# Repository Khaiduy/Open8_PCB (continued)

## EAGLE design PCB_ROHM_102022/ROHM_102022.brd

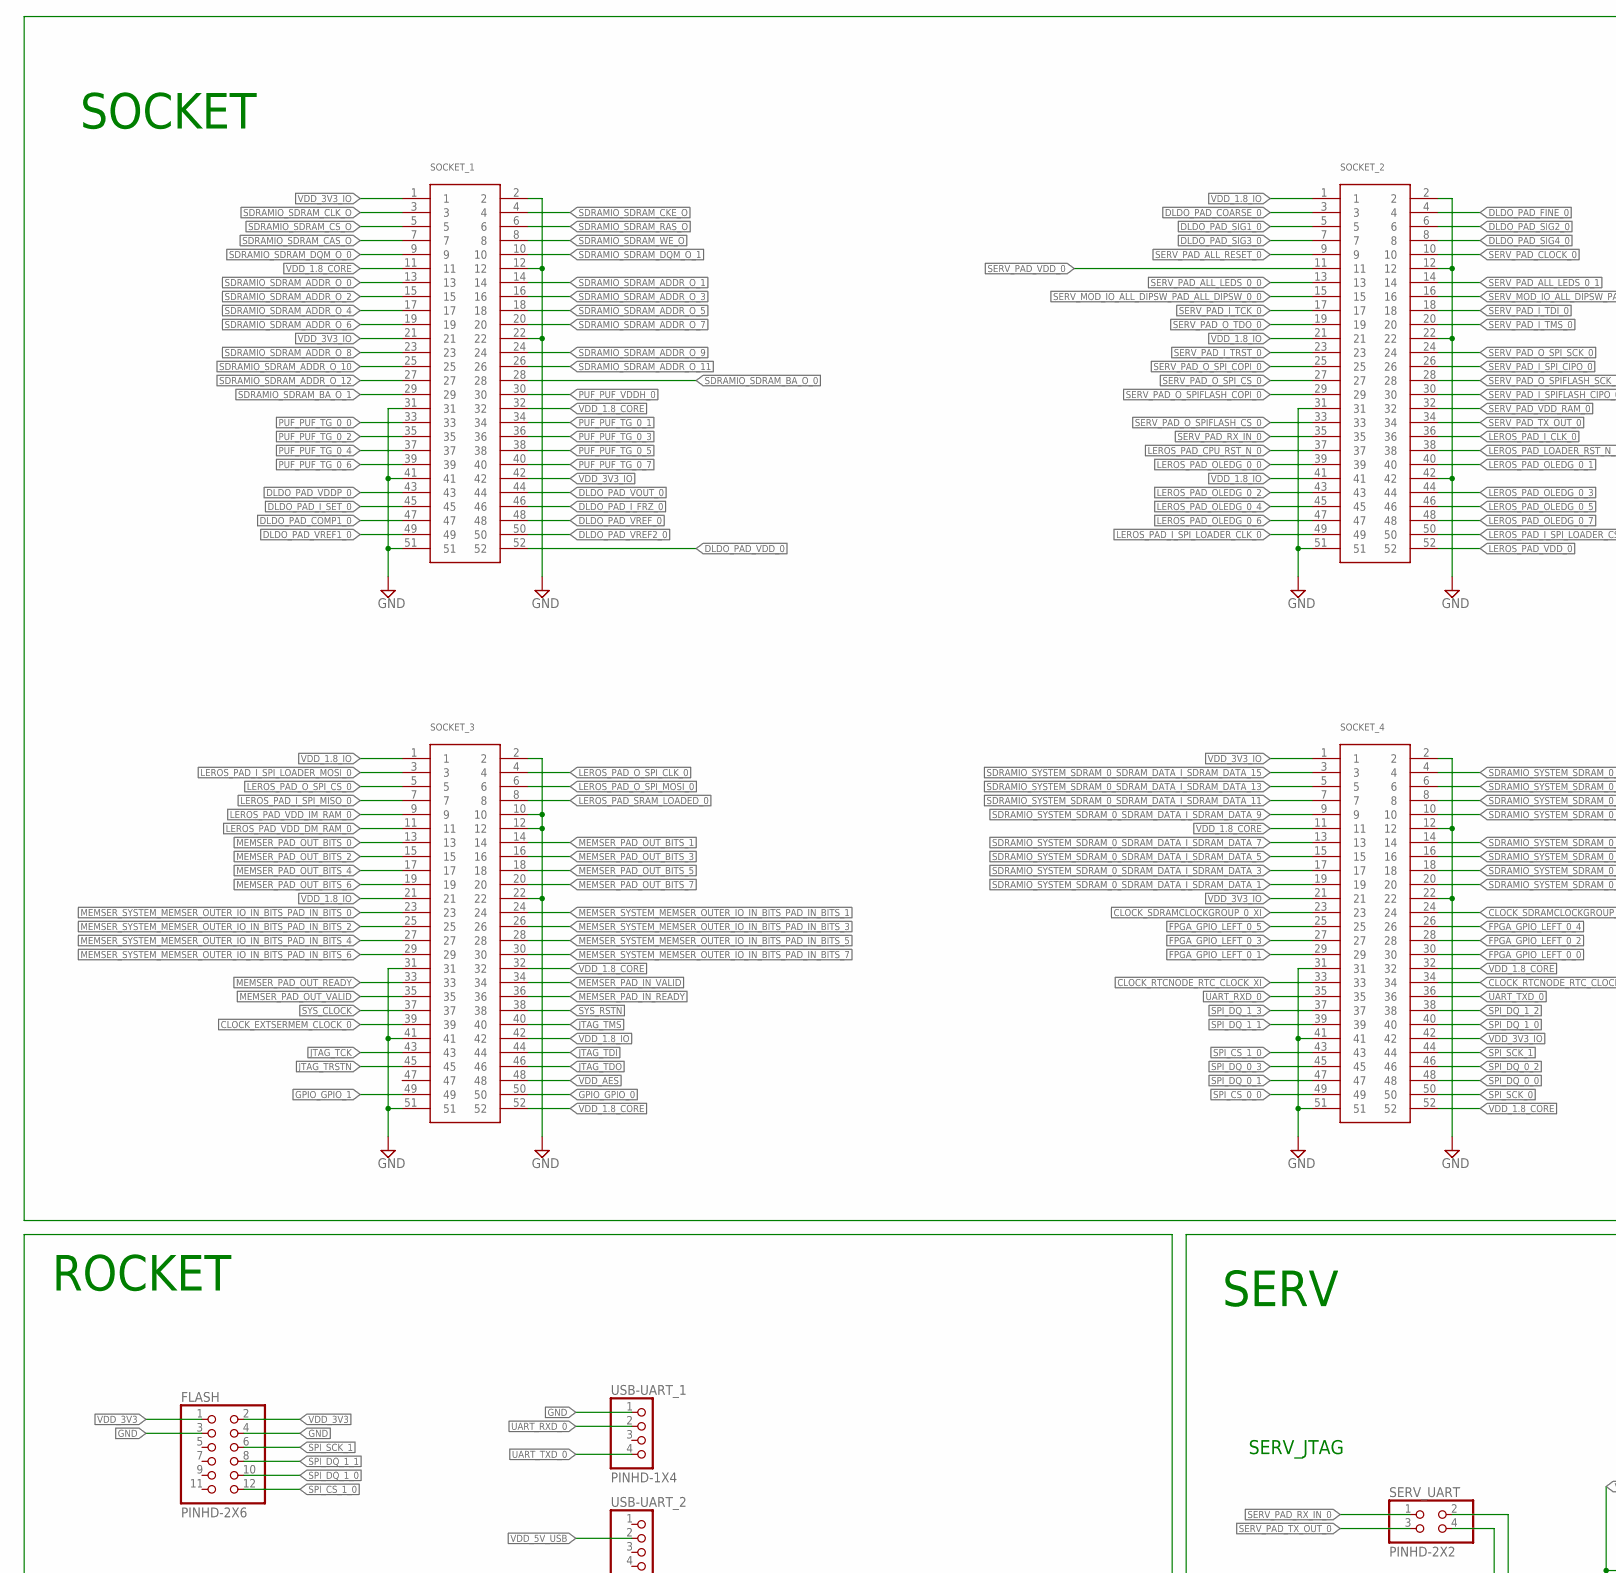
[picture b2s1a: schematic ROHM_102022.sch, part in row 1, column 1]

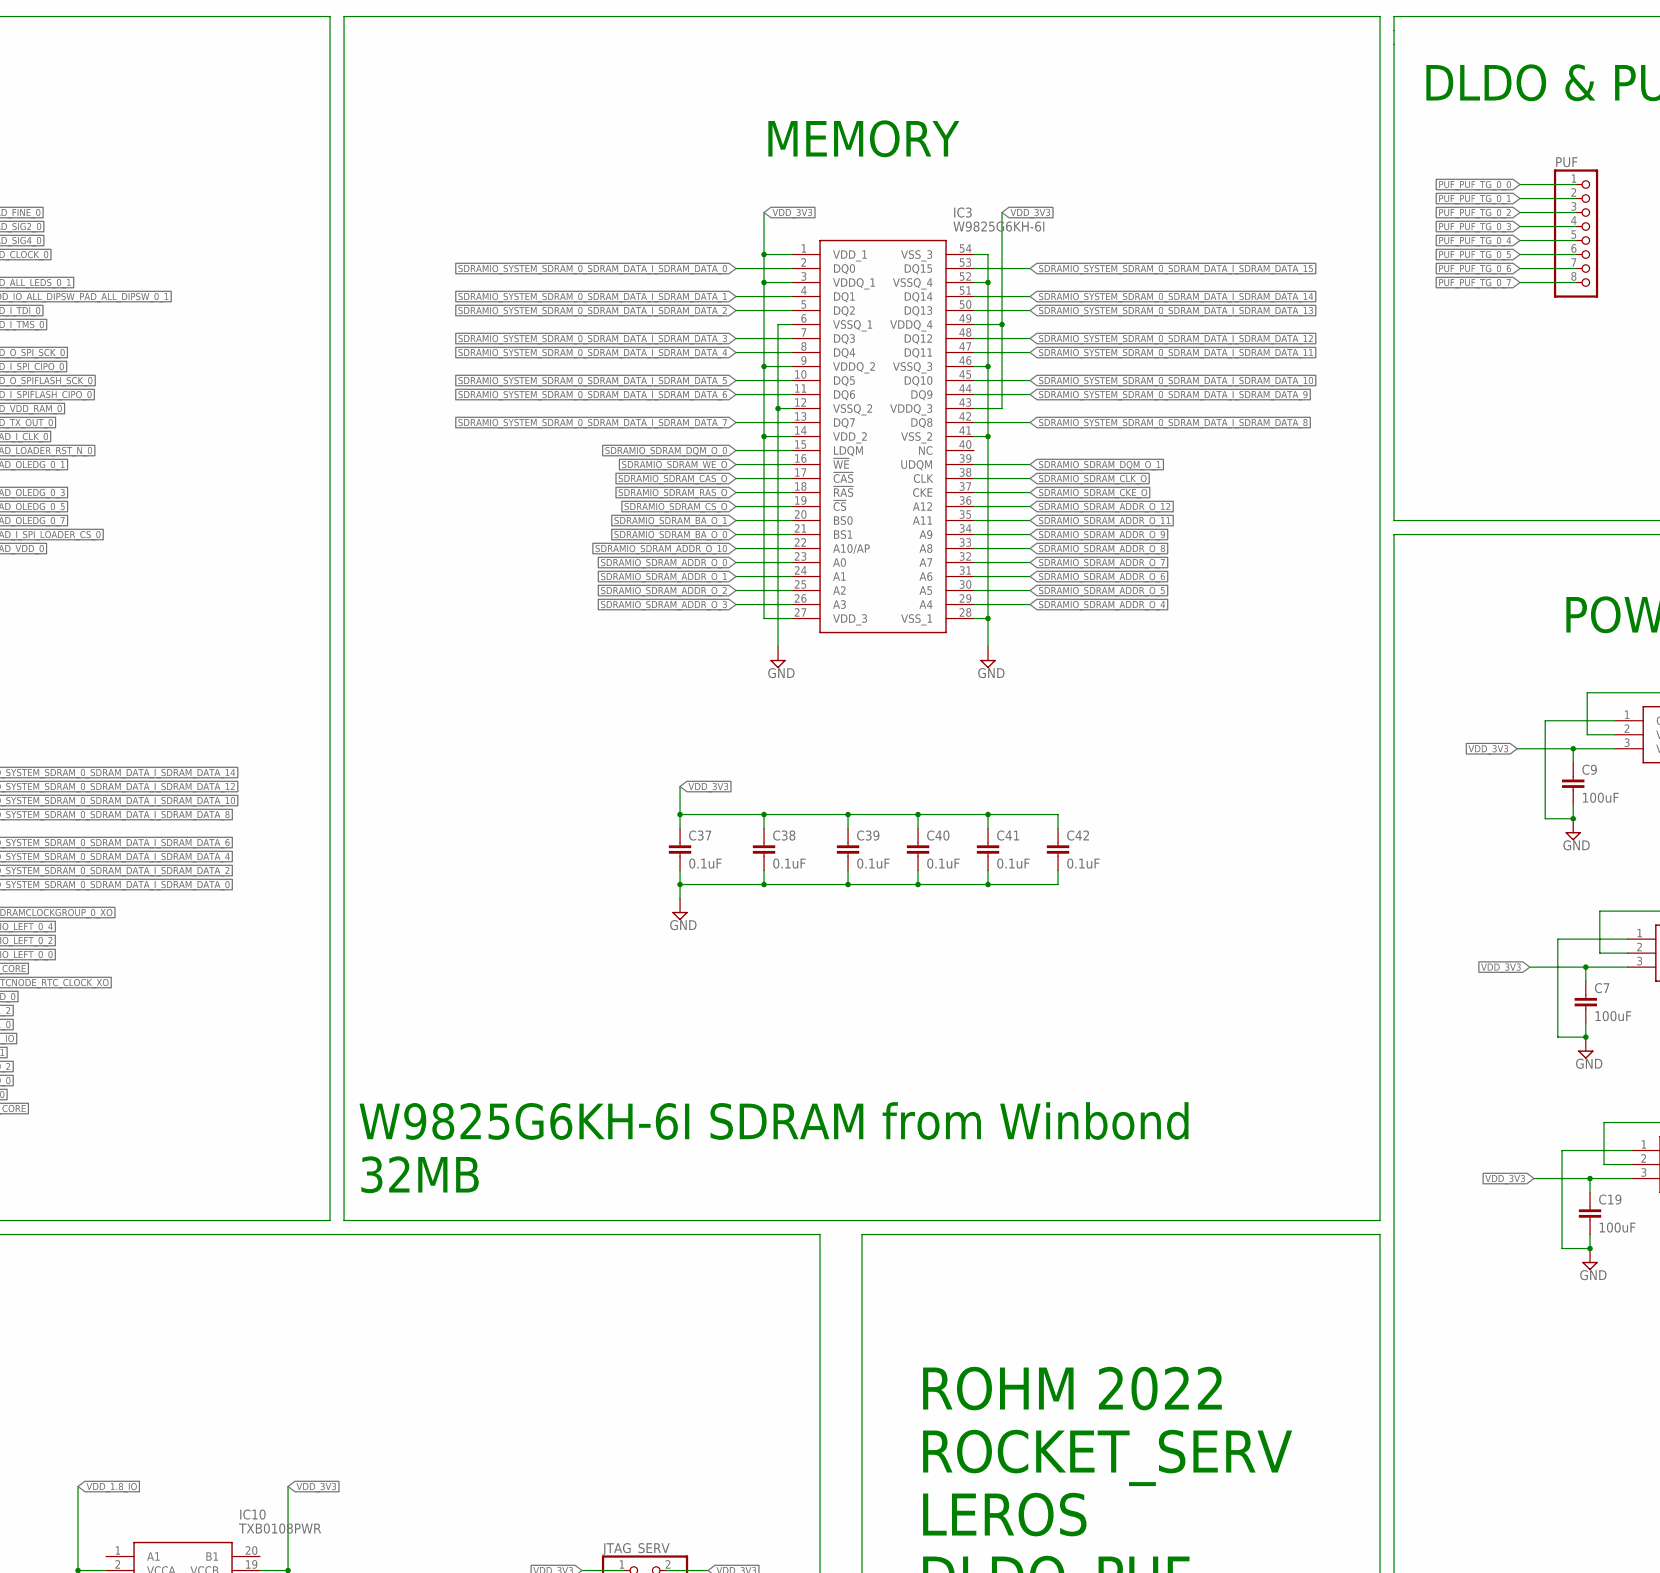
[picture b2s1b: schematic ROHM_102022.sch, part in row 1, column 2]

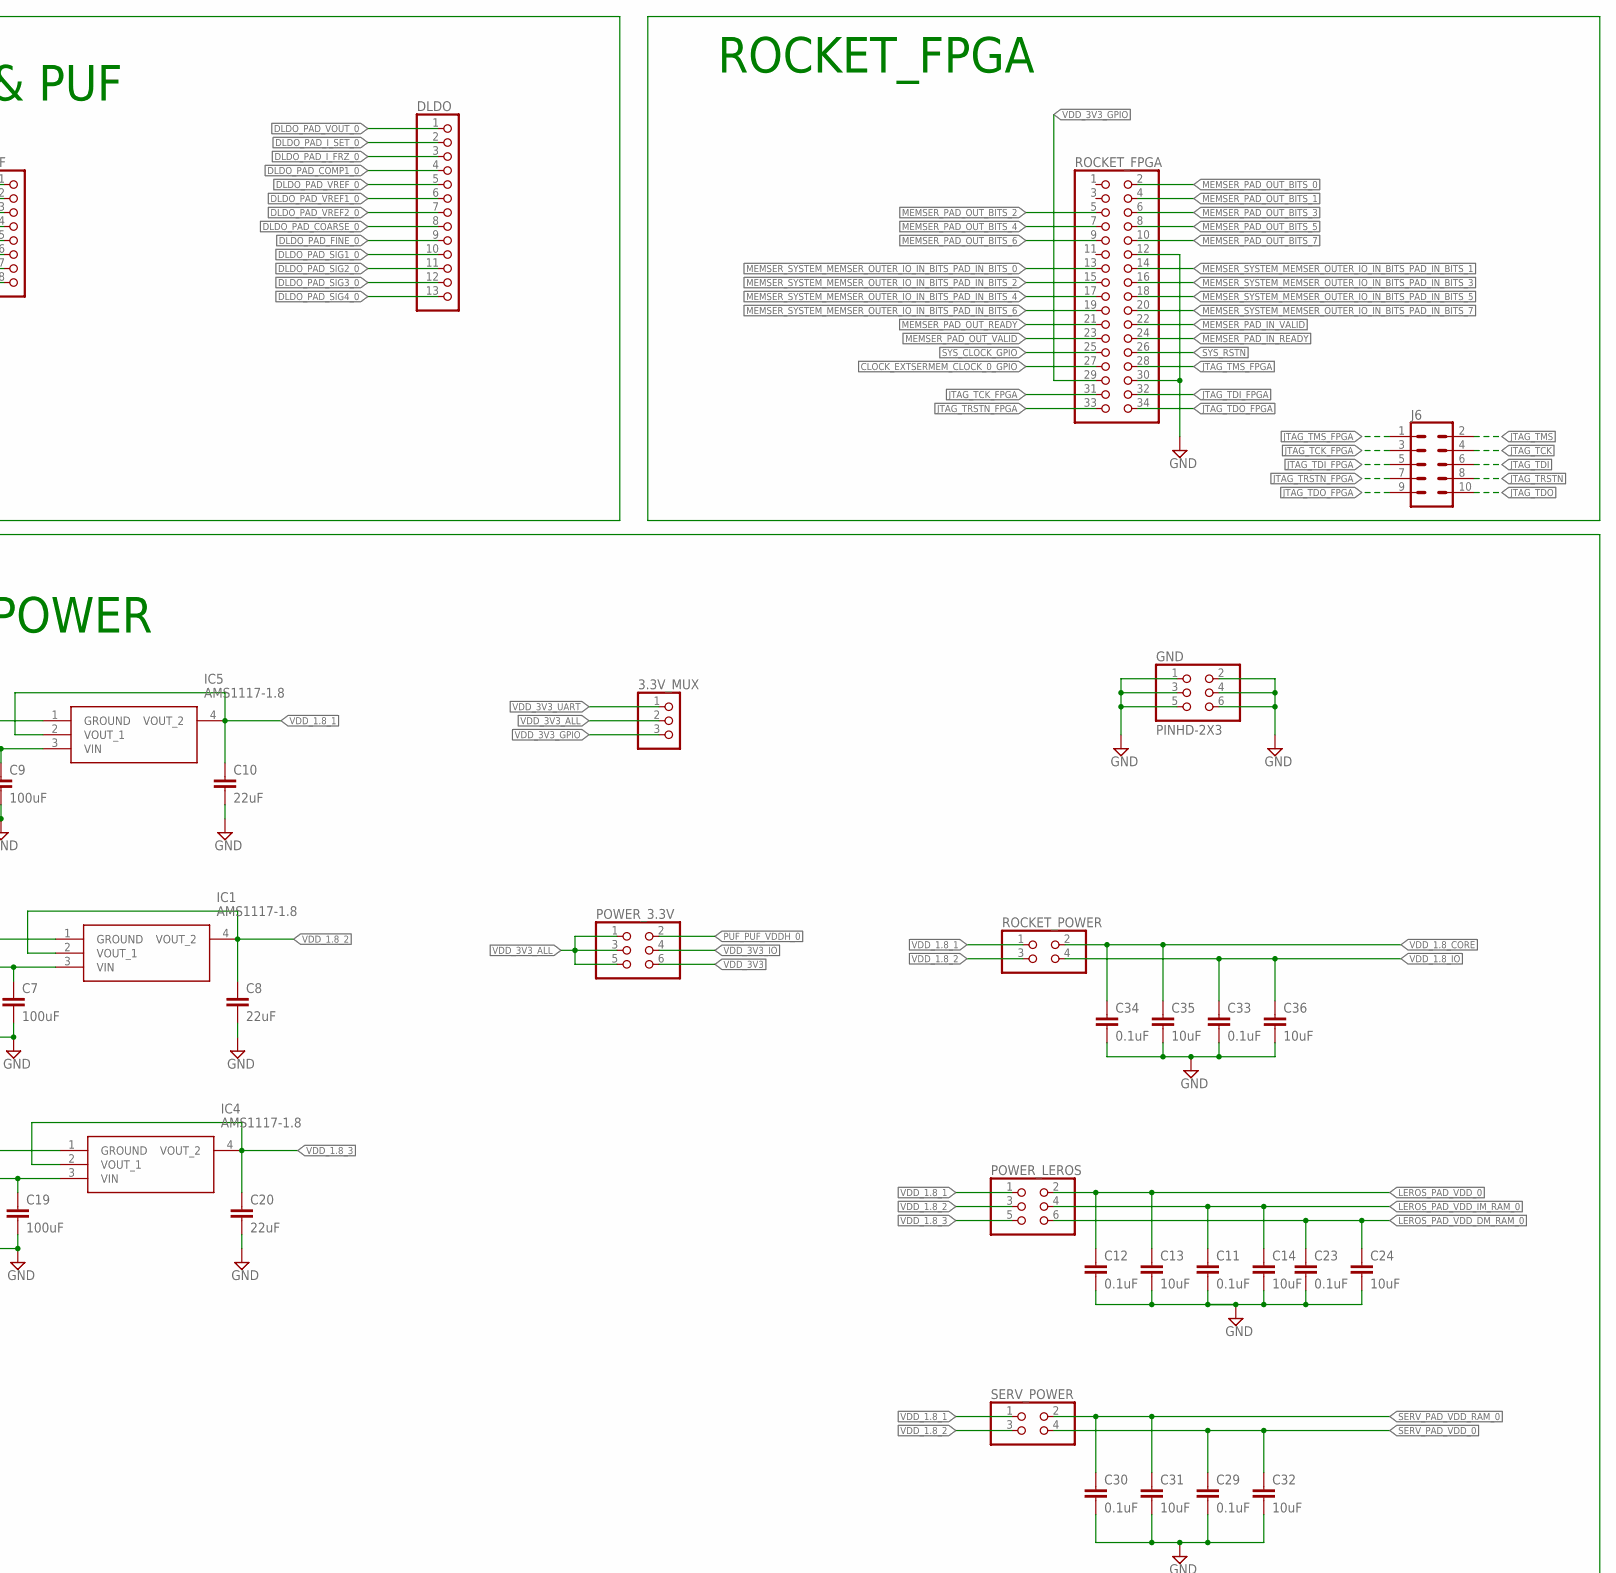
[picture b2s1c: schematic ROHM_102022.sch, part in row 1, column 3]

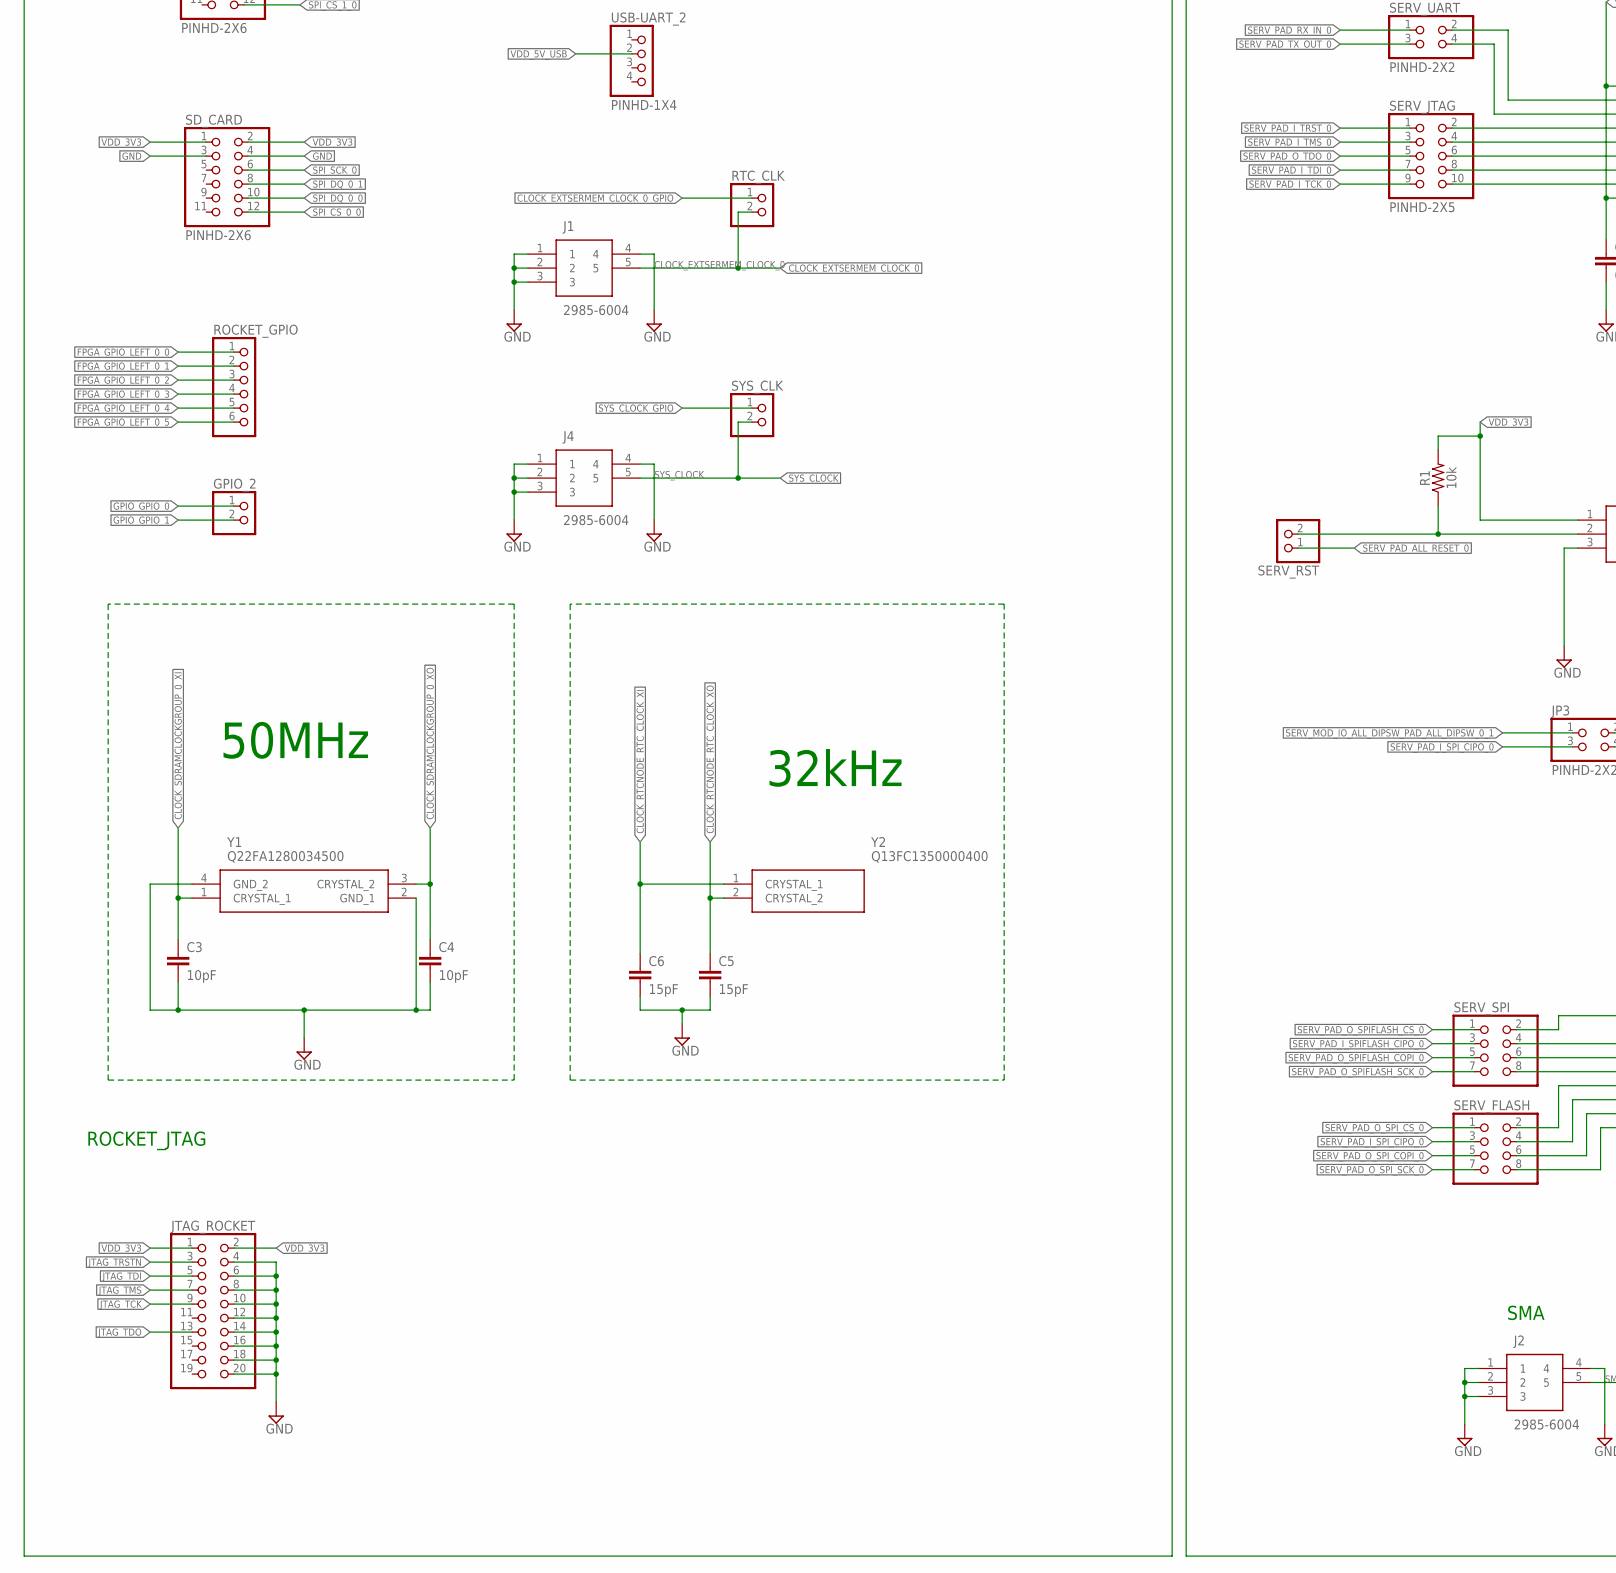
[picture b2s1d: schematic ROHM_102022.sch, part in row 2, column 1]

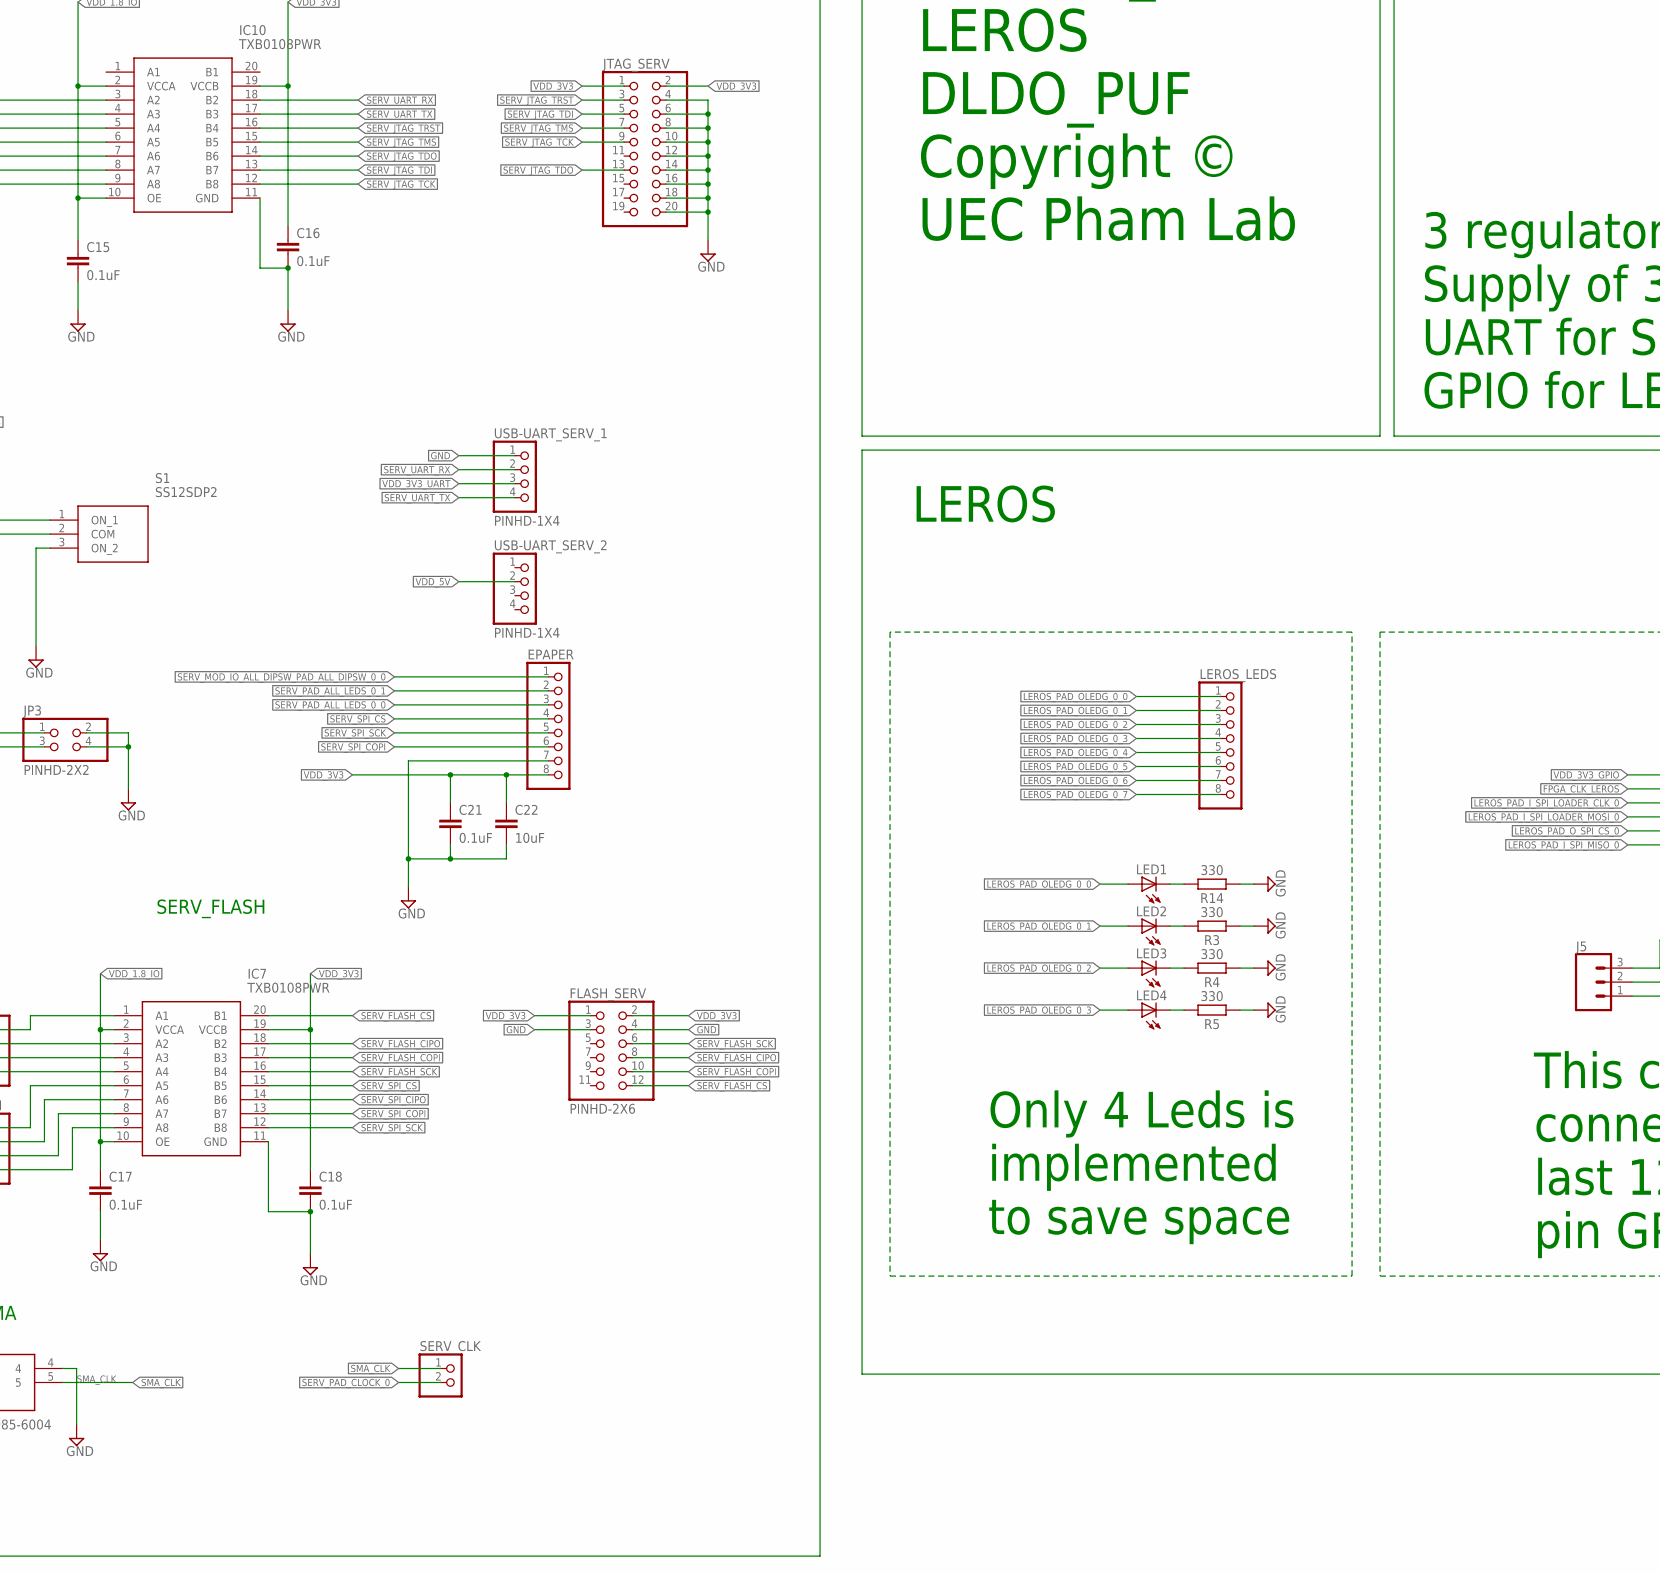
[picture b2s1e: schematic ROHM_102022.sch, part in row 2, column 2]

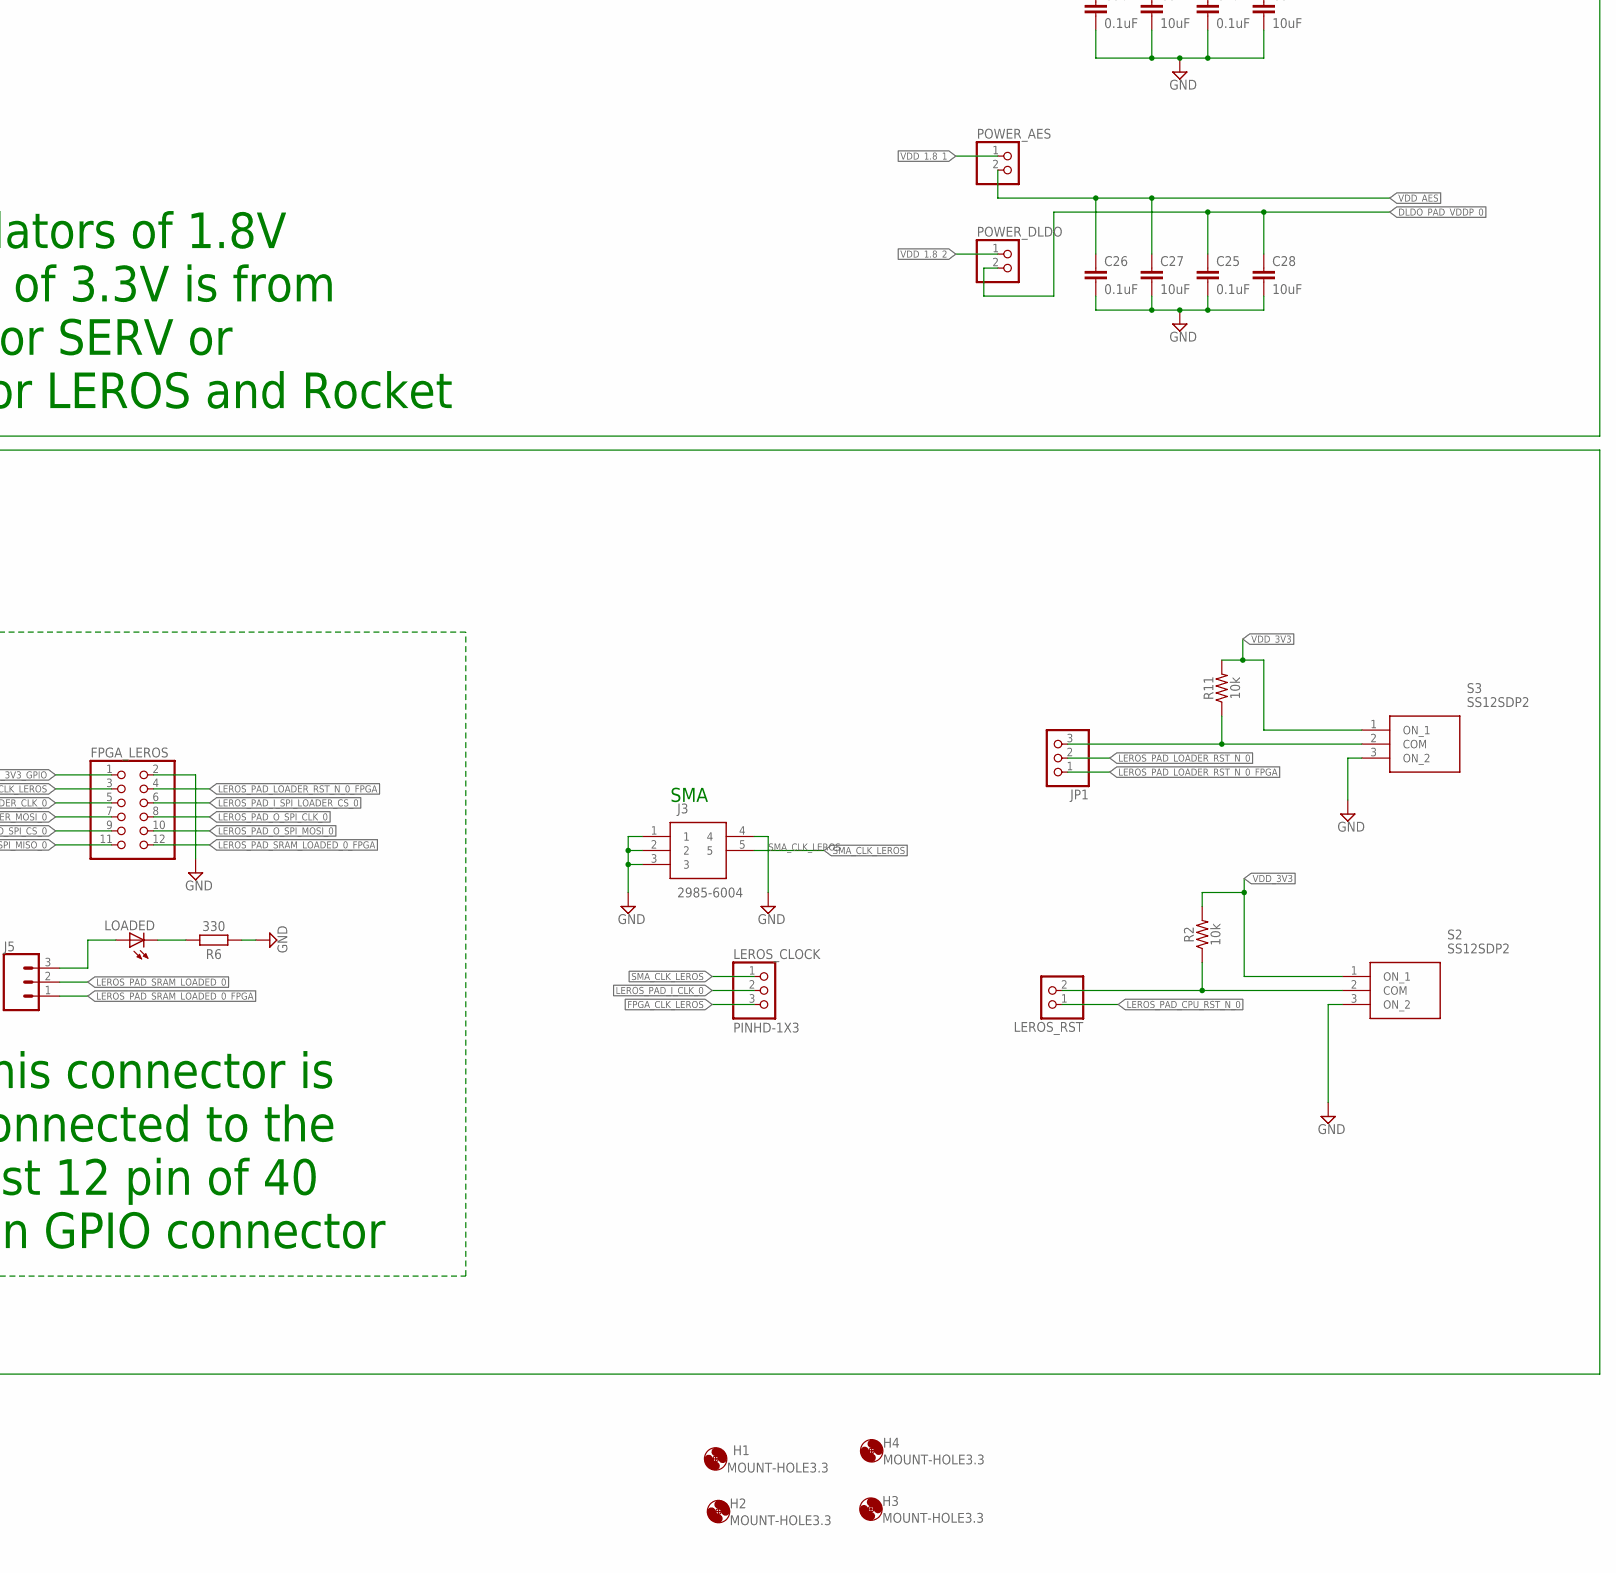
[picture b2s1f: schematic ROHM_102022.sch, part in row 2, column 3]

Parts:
3.3V_MUX: PINHD-1X3; 1X03
C3, C4: 10pF; 1206
C5, C6: 15pF; 1206
C7, C9, C19: 100uF; 1206
C8, C10, C20: 22uF; 1206
C11, C12, C15, C16, C17, C18, C21, C23, C25, C26, C29, C30, C33, C34, C37, C38, C39, C40, C41, C42: 0.1uF; 1206
C13, C14, C22, C24, C27, C28, C31, C32, C35, C36: 10uF; 1206
DLDO: PINHD-1X13; 1X13
EPAPER: PINHD-1X8; 1X08
FLASH: PINHD-2X6; 2X06
FLASH_SERV: PINHD-2X6; 2X06
FPGA_LEROS: PINHD-2X6; 2X06
GND: PINHD-2X3; 2X03
GPIO_2: PINHD-1X2; 1X02
H1, H2, H3, H4: MOUNT-HOLE3.3; 3,3
IC1, IC4, IC5: AMS1117-1.8; SOT229P700X180-4N
IC3: W9825G6KH-6I; SOP80P1176X120-54N
IC7, IC10: TXB0108PWR; SOP65P640X120-20N
J1, J2, J3, J4: 2985-6004; 29856004
J5: CONN_03; 1X03
J6: CONN_05X2PTH; 2X5
JP1: PINHD-1X3; 1X03
JP3: PINHD-2X2; 2X02
JTAG_ROCKET: PINHD-2X10; 2X10
JTAG_SERV: PINHD-2X10; 2X10
LED1, LED2, LED3, LED4: LEDCHIPLED_0805; CHIPLED_0805
LEROS_CLOCK: PINHD-1X3; 1X03
LEROS_LEDS: PINHD-1X8; 1X08
LEROS_RST: PINHD-1X2; 1X02
LOADED: LEDCHIPLED_0805; CHIPLED_0805
POWER_3.3V: PINHD-2X3; 2X03
POWER_AES: PINHD-1X2; 1X02
POWER_DLDO: PINHD-1X2; 1X02
POWER_LEROS: PINHD-2X3; 2X03
PUF: PINHD-1X8; 1X08
R1, R2, R11: 10k; 1206
R3, R4, R5, R6, R14: 330; RESC3216X70
ROCKET_FPGA: PINHD-2X17; 2X17
ROCKET_GPIO: PINHD-1X6; 1X06
ROCKET_POWER: PINHD-2X2; 2X02
RTC_CLK: PINHD-1X2; 1X02
S1, S2, S3: SS12SDP2
SD_CARD: PINHD-2X6; 2X06
SERV_CLK: PINHD-1X2; 1X02
SERV_FLASH: PINHD-2X4; 2X04
SERV_JTAG: PINHD-2X5; 2X05
SERV_POWER: PINHD-2X2; 2X02
SERV_RST: PINHD-1X2; 1X02
SERV_SPI: PINHD-2X4; 2X04
SERV_UART: PINHD-2X2; 2X02
SOCKET_1, SOCKET_2, SOCKET_3, SOCKET_4: 2X26_HEADER
SYS_CLK: PINHD-1X2; 1X02
USB-UART_1, USB-UART_2: PINHD-1X4; 1X04
USB-UART_SERV_1, USB-UART_SERV_2: PINHD-1X4; 1X04
Y1: Q22FA1280034500
Y2: Q13FC1350000400

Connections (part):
CLOCK_EXTSERMEM_CLOCK_0: J1.5, RTC_CLK.2, SOCKET_3.39
CLOCK_EXTSERMEM_CLOCK_0_GPIO: ROCKET_FPGA.27, RTC_CLK.1
CLOCK_RTCNODE_RTC_CLOCK_XI: C6.1, SOCKET_4.33, Y2.1 (CRYSTAL_1)
CLOCK_RTCNODE_RTC_CLOCK_XO: C5.1, SOCKET_4.34, Y2.2 (CRYSTAL_2)
CLOCK_SDRAMCLOCKGROUP_0_XI: C3.1, SOCKET_4.23, Y1.1 (CRYSTAL_1)
CLOCK_SDRAMCLOCKGROUP_0_XO: C4.1, SOCKET_4.24, Y1.3 (CRYSTAL_2)
DLDO_PAD_COARSE_0: DLDO.8, SOCKET_2.3
DLDO_PAD_COMP1_0: DLDO.4, SOCKET_1.47
DLDO_PAD_FINE_0: DLDO.9, SOCKET_2.4
DLDO_PAD_I_FRZ_0: DLDO.3, SOCKET_1.46
DLDO_PAD_I_SET_0: DLDO.2, SOCKET_1.45
DLDO_PAD_SIG1_0: DLDO.10, SOCKET_2.5
DLDO_PAD_SIG2_0: DLDO.11, SOCKET_2.6
DLDO_PAD_SIG3_0: DLDO.12, SOCKET_2.7
DLDO_PAD_SIG4_0: DLDO.13, SOCKET_2.8
DLDO_PAD_VDDP_0: C25.1, C28.1, POWER_DLDO.2, SOCKET_1.43
DLDO_PAD_VDD_0: SOCKET_1.52
DLDO_PAD_VOUT_0: DLDO.1, SOCKET_1.44
DLDO_PAD_VREF1_0: DLDO.6, SOCKET_1.49
DLDO_PAD_VREF2_0: DLDO.7, SOCKET_1.50
DLDO_PAD_VREF_0: DLDO.5, SOCKET_1.48
FPGA_CLK_LEROS: FPGA_LEROS.3, LEROS_CLOCK.3
FPGA_GPIO_LEFT_0_0: ROCKET_GPIO.1, SOCKET_4.30
FPGA_GPIO_LEFT_0_1: ROCKET_GPIO.2, SOCKET_4.29
FPGA_GPIO_LEFT_0_2: ROCKET_GPIO.3, SOCKET_4.28
FPGA_GPIO_LEFT_0_3: ROCKET_GPIO.4, SOCKET_4.27
FPGA_GPIO_LEFT_0_4: ROCKET_GPIO.5, SOCKET_4.26
FPGA_GPIO_LEFT_0_5: ROCKET_GPIO.6, SOCKET_4.25
GND: C3.2, C4.2, C5.2, C6.2, C7.2, C8.2, C9.2, C10.2, C11.2, C12.2, C13.2, C14.2, C15.2, C16.2, C17.2, C18.2, C19.2, C20.2, C21.2, C22.2, C23.2, C24.2, C25.2, C26.2, C27.2, C28.2, C29.2, C30.2, C31.2, C32.2, C33.2, C34.2, C35.2, C36.2, C37.2, C38.2, C39.2, C40.2, C41.2, C42.2, EPAPER.7, FLASH.3, FLASH.4, FLASH_SERV.3, FLASH_SERV.4, FPGA_LEROS.2, GND.1, GND.2, GND.3, GND.4, GND.5, GND.6, IC1.1 (GROUND), IC3.6 (VSSQ_1), IC3.12 (VSSQ_2), IC3.28 (VSS_1), IC3.41 (VSS_2), IC3.46 (VSSQ_3), IC3.52 (VSSQ_4), IC3.54 (VSS_3), IC4.1 (GROUND), IC5.1 (GROUND), IC7.11 (GND), IC10.11 (GND), J1.1, J1.2, J1.3, J1.4, J2.1, J2.2, J2.3, J2.4, J3.1, J3.2, J3.3, J3.4, J4.1, J4.2, J4.3, J4.4, JP3.2, JP3.4, JTAG_ROCKET.4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
GPIO_GPIO_0: GPIO_2.1, SOCKET_3.50
GPIO_GPIO_1: GPIO_2.2, SOCKET_3.49
JTAG_TCK: J6.4, JTAG_ROCKET.9, SOCKET_3.43
JTAG_TCK_FPGA: J6.3, ROCKET_FPGA.31
JTAG_TDI: J6.6, JTAG_ROCKET.5, SOCKET_3.44
JTAG_TDI_FPGA: J6.5, ROCKET_FPGA.32
JTAG_TDO: J6.10, JTAG_ROCKET.13, SOCKET_3.46
JTAG_TDO_FPGA: J6.9, ROCKET_FPGA.34
JTAG_TMS: J6.2, JTAG_ROCKET.7, SOCKET_3.40
JTAG_TMS_FPGA: J6.1, ROCKET_FPGA.28
JTAG_TRSTN: J6.8, JTAG_ROCKET.3, SOCKET_3.45
JTAG_TRSTN_FPGA: J6.7, ROCKET_FPGA.33
LEROS_PAD_CPU_RST_N_0: LEROS_RST.1, SOCKET_2.37
LEROS_PAD_I_CLK_0: LEROS_CLOCK.2, SOCKET_2.36
LEROS_PAD_I_SPI_LOADER_CLK_0: FPGA_LEROS.5, SOCKET_2.49
LEROS_PAD_I_SPI_LOADER_CS_0: FPGA_LEROS.6, SOCKET_2.50
LEROS_PAD_I_SPI_LOADER_MOSI_0: FPGA_LEROS.7, SOCKET_3.3
LEROS_PAD_I_SPI_MISO_0: FPGA_LEROS.11, SOCKET_3.7
LEROS_PAD_LOADER_RST_N_0: JP1.2, SOCKET_2.38
LEROS_PAD_LOADER_RST_N_0_FPGA: FPGA_LEROS.4, JP1.1
LEROS_PAD_OLEDG_0_0: LED1.A, LEROS_LEDS.1, SOCKET_2.39
LEROS_PAD_OLEDG_0_1: LED2.A, LEROS_LEDS.2, SOCKET_2.40
LEROS_PAD_OLEDG_0_2: LED3.A, LEROS_LEDS.3, SOCKET_2.43
LEROS_PAD_OLEDG_0_3: LED4.A, LEROS_LEDS.4, SOCKET_2.44
LEROS_PAD_OLEDG_0_4: LEROS_LEDS.5, SOCKET_2.45
LEROS_PAD_OLEDG_0_5: LEROS_LEDS.6, SOCKET_2.46
LEROS_PAD_OLEDG_0_6: LEROS_LEDS.7, SOCKET_2.47
LEROS_PAD_OLEDG_0_7: LEROS_LEDS.8, SOCKET_2.48
LEROS_PAD_O_SPI_CLK_0: FPGA_LEROS.8, SOCKET_3.4
LEROS_PAD_O_SPI_CS_0: FPGA_LEROS.9, SOCKET_3.5
LEROS_PAD_O_SPI_MOSI_0: FPGA_LEROS.10, SOCKET_3.6
LEROS_PAD_SRAM_LOADED_0: J5.2, SOCKET_3.8
LEROS_PAD_SRAM_LOADED_0_FPGA: FPGA_LEROS.12, J5.1
LEROS_PAD_VDD_0: C12.1, C13.1, POWER_LEROS.2, SOCKET_2.52
LEROS_PAD_VDD_DM_RAM_0: C23.1, C24.1, POWER_LEROS.6, SOCKET_3.11
LEROS_PAD_VDD_IM_RAM_0: C11.1, C14.1, POWER_LEROS.4, SOCKET_3.9
MEMSER_PAD_IN_READY: ROCKET_FPGA.24, SOCKET_3.36
MEMSER_PAD_IN_VALID: ROCKET_FPGA.22, SOCKET_3.34
MEMSER_PAD_OUT_BITS_0: ROCKET_FPGA.2, SOCKET_3.13
MEMSER_PAD_OUT_BITS_1: ROCKET_FPGA.4, SOCKET_3.14
MEMSER_PAD_OUT_BITS_2: ROCKET_FPGA.5, SOCKET_3.15
MEMSER_PAD_OUT_BITS_3: ROCKET_FPGA.6, SOCKET_3.16
MEMSER_PAD_OUT_BITS_4: ROCKET_FPGA.7, SOCKET_3.17
MEMSER_PAD_OUT_BITS_5: ROCKET_FPGA.8, SOCKET_3.18
MEMSER_PAD_OUT_BITS_6: ROCKET_FPGA.9, SOCKET_3.19
MEMSER_PAD_OUT_BITS_7: ROCKET_FPGA.10, SOCKET_3.20
MEMSER_PAD_OUT_READY: ROCKET_FPGA.21, SOCKET_3.33
MEMSER_PAD_OUT_VALID: ROCKET_FPGA.23, SOCKET_3.35
MEMSER_SYSTEM_MEMSER_OUTER_IO_IN_BITS_PAD_IN_BITS_0: ROCKET_FPGA.13, SOCKET_3.23
MEMSER_SYSTEM_MEMSER_OUTER_IO_IN_BITS_PAD_IN_BITS_1: ROCKET_FPGA.14, SOCKET_3.24
MEMSER_SYSTEM_MEMSER_OUTER_IO_IN_BITS_PAD_IN_BITS_2: ROCKET_FPGA.15, SOCKET_3.25
MEMSER_SYSTEM_MEMSER_OUTER_IO_IN_BITS_PAD_IN_BITS_3: ROCKET_FPGA.16, SOCKET_3.26
MEMSER_SYSTEM_MEMSER_OUTER_IO_IN_BITS_PAD_IN_BITS_4: ROCKET_FPGA.17, SOCKET_3.27
MEMSER_SYSTEM_MEMSER_OUTER_IO_IN_BITS_PAD_IN_BITS_5: ROCKET_FPGA.18, SOCKET_3.28
MEMSER_SYSTEM_MEMSER_OUTER_IO_IN_BITS_PAD_IN_BITS_6: ROCKET_FPGA.19, SOCKET_3.29
MEMSER_SYSTEM_MEMSER_OUTER_IO_IN_BITS_PAD_IN_BITS_7: ROCKET_FPGA.20, SOCKET_3.30
unnamed: IC7.1 (A1), SERV_SPI.2
unnamed: LED1.C, R14.2
unnamed: IC7.3 (A2), SERV_SPI.4
unnamed: IC7.4 (A3), SERV_SPI.6
unnamed: IC7.5 (A4), SERV_SPI.8
unnamed: JP1.3, R11.1, S3.2 (COM)
unnamed: LED2.C, R3.2
unnamed: LED3.C, R4.2
unnamed: LED4.C, R5.2
unnamed: IC7.6 (A5), SERV_FLASH.2
unnamed: IC7.7 (A6), SERV_FLASH.4
unnamed: IC7.8 (A7), SERV_FLASH.6
unnamed: IC7.9 (A8), SERV_FLASH.8
unnamed: LOADED.C, R6.2
unnamed: J5.3, LOADED.A
unnamed: IC10.9 (A8), SERV_JTAG.10
unnamed: IC10.8 (A7), SERV_JTAG.8
unnamed: IC10.7 (A6), SERV_JTAG.6
unnamed: IC10.6 (A5), SERV_JTAG.4
unnamed: IC10.5 (A4), SERV_JTAG.2
unnamed: IC10.4 (A3), SERV_UART.4
unnamed: IC10.3 (A2), SERV_UART.2
PUF_PUF_TG_0_0: PUF.1, SOCKET_1.33
PUF_PUF_TG_0_1: PUF.2, SOCKET_1.34
PUF_PUF_TG_0_2: PUF.3, SOCKET_1.35
PUF_PUF_TG_0_3: PUF.4, SOCKET_1.36
PUF_PUF_TG_0_4: PUF.5, SOCKET_1.37
PUF_PUF_TG_0_5: PUF.6, SOCKET_1.38
PUF_PUF_TG_0_6: PUF.7, SOCKET_1.39
PUF_PUF_TG_0_7: PUF.8, SOCKET_1.40
PUF_PUF_VDDH_0: POWER_3.3V.2, SOCKET_1.30
RST_SW: R1.1, S1.2 (COM), SERV_RST.2
RST_SW1: LEROS_RST.2, R2.1, S2.2 (COM)
SDRAMIO_SDRAM_ADDR_O_0: IC3.23 (A0), SOCKET_1.13
SDRAMIO_SDRAM_ADDR_O_1: IC3.24 (A1), SOCKET_1.14
SDRAMIO_SDRAM_ADDR_O_2: IC3.25 (A2), SOCKET_1.15
SDRAMIO_SDRAM_ADDR_O_3: IC3.26 (A3), SOCKET_1.16
SDRAMIO_SDRAM_ADDR_O_4: IC3.29 (A4), SOCKET_1.17
SDRAMIO_SDRAM_ADDR_O_5: IC3.30 (A5), SOCKET_1.18
SDRAMIO_SDRAM_ADDR_O_6: IC3.31 (A6), SOCKET_1.19
SDRAMIO_SDRAM_ADDR_O_7: IC3.32 (A7), SOCKET_1.20
SDRAMIO_SDRAM_ADDR_O_8: IC3.33 (A8), SOCKET_1.23
SDRAMIO_SDRAM_ADDR_O_9: IC3.34 (A9), SOCKET_1.24
SDRAMIO_SDRAM_ADDR_O_10: IC3.22 (A10/AP), SOCKET_1.25
SDRAMIO_SDRAM_ADDR_O_11: IC3.35 (A11), SOCKET_1.26
SDRAMIO_SDRAM_ADDR_O_12: IC3.36 (A12), SOCKET_1.27
SDRAMIO_SDRAM_BA_O_0: IC3.21 (BS1), SOCKET_1.28
SDRAMIO_SDRAM_BA_O_1: IC3.20 (BS0), SOCKET_1.29
SDRAMIO_SDRAM_CAS_O: IC3.17 (!CAS), SOCKET_1.7
SDRAMIO_SDRAM_CKE_O: IC3.37 (CKE), SOCKET_1.4
SDRAMIO_SDRAM_CLK_O: IC3.38 (CLK), SOCKET_1.3
SDRAMIO_SDRAM_CS_O: IC3.19 (!CS), SOCKET_1.5
SDRAMIO_SDRAM_DQM_O_0: IC3.15 (LDQM), SOCKET_1.9
SDRAMIO_SDRAM_DQM_O_1: IC3.39 (UDQM), SOCKET_1.10
SDRAMIO_SDRAM_RAS_O: IC3.18 (!RAS), SOCKET_1.6
SDRAMIO_SDRAM_WE_O: IC3.16 (!WE), SOCKET_1.8
SDRAMIO_SYSTEM_SDRAM_0_SDRAM_DATA_I_SDRAM_DATA_0: IC3.2 (DQ0), SOCKET_4.20
SDRAMIO_SYSTEM_SDRAM_0_SDRAM_DATA_I_SDRAM_DATA_1: IC3.4 (DQ1), SOCKET_4.19
SDRAMIO_SYSTEM_SDRAM_0_SDRAM_DATA_I_SDRAM_DATA_2: IC3.5 (DQ2), SOCKET_4.18
SDRAMIO_SYSTEM_SDRAM_0_SDRAM_DATA_I_SDRAM_DATA_3: IC3.7 (DQ3), SOCKET_4.17
SDRAMIO_SYSTEM_SDRAM_0_SDRAM_DATA_I_SDRAM_DATA_4: IC3.8 (DQ4), SOCKET_4.16
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
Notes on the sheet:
SERV_JTAG
SERV_FLASH
SMA
SERV
LEROS
SOCKET
MEMORY
DLDO & PUF
ROCKET_FPGA
POWER
ROCKET
ROHM 2022 ROCKET_SERV LEROS DLDO_PUF Copyright © UEC Pham Lab
W9825G6KH-6I SDRAM from Winbond 32MB
3 regulators of 1.8V Supply of 3.3V is from UART for SERV or GPIO for LEROS and Rocket
Only 4 Leds is implemented to save space
This connector is connected to the last 12 pin of 40 pin GPIO connector
50MHz
32kHz
ROCKET_JTAG

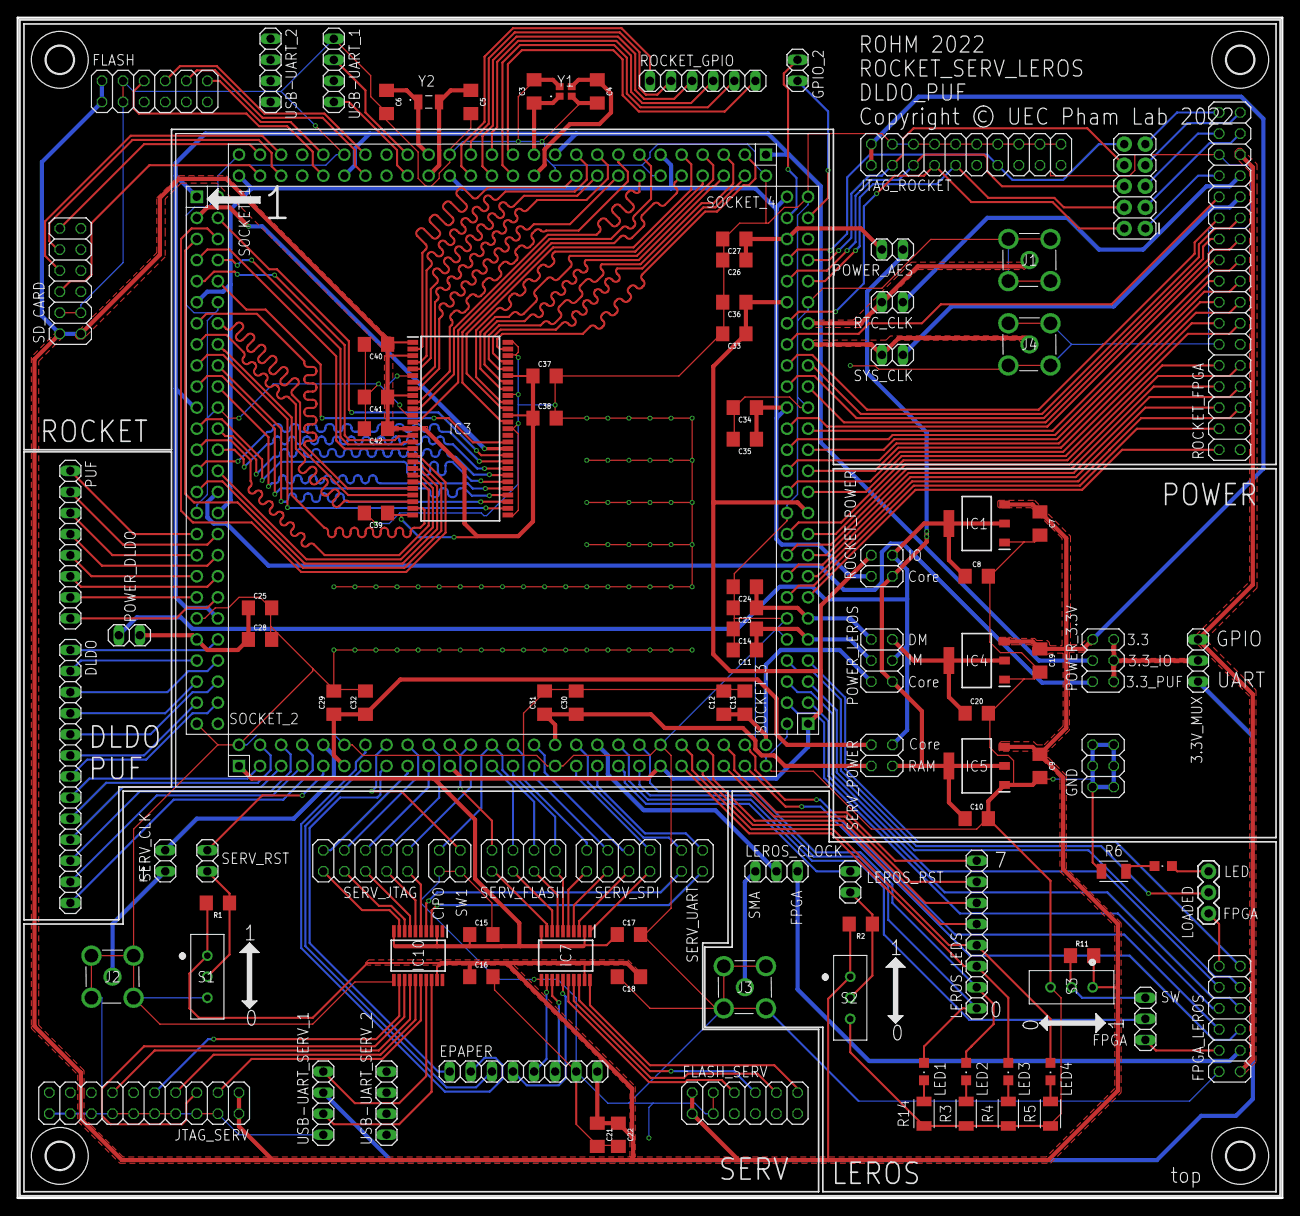
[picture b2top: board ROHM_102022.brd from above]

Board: 2 copper layers, 152.4 x 142.2 mm, 115 parts (0 on the bottom side), 219 nets.
